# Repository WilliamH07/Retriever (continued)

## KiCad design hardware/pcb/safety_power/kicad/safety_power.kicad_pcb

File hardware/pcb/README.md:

# Printed circuit boards

Three boards, **redesigned from a clean sheet and drawn in KiCad 10**. ERC, DRC
and schematic parity are at zero on all three; none has been fabricated yet.

| Read | For |
|---|---|
| [`etat-des-lieux.md`](etat-des-lieux.md) | Status of all three, what blocks each, what an expert must review (French) |
| [`simulations.md`](simulations.md) | ngspice results for the chopper, precharge, Hall tap, VR and eFuses (French) |
| [`conception-v2.md`](conception-v2.md) | The cross-board brief: why v1 failed, principles, decisions D1–D9 (French) |
| [`outils.md`](outils.md) | The toolchain: KiCad 10 driven from the command line, the Python generator |

The first
pass (August–September 2026, EasyEDA) is archived in
[`docs/archive/pcb-v1/`](../../docs/archive/pcb-v1/): its schematic was never
functional, and parts of its specification contradicted the v1.2 corrections.

| Board | Role | Copies | Blocked by | Design brief |
|---|---|---|---|---|
| `safety_bus_distribution` | Passive CAN + `/SAFE` trunk, protected 5 V per node, no MCU | 1 of 5 | nothing — **v2.0**, ready to order | [decisions](safety_bus_distribution/decisions.md) · [brief](safety_bus_distribution/cahier-des-charges.md) |
| `motor_interface` | Hall tap to the ESP32, command path VR / DIR / EL / STOP to two ZS-X11H | 2 of 5 | **v2.0-draft**; M7, HALL_OC, P1–P3 | [decisions](motor_interface/decisions.md) · [brief](motor_interface/cahier-des-charges.md) |
| `safety_power` | Battery input, static contactor, precharge, brake chopper, INA228, DC/DC rails, SAFETY ESP32 | 1 of 5 | **v2.0-draft**; M1, M2, M10, M12, PACK_ID, P1–P3, expert review | [decisions](safety_power/decisions.md) · [brief](safety_power/cahier-des-charges.md) |

Two single-board studies for the PCBWay sponsorship (`mainboard`, `logic_board`) are
kept in [`prototypage/`](prototypage/): neither fits the 60 € budget.

Build order, from [`11-corrections-v1.2.md`](../../docs/architecture/11-corrections-v1.2.md)
part 6:

```
1  safety_bus_distribution   no blocking measurement, unlocks the CAN bench
2  M4, M5, M7 on one motor and one ZS-X11H, current-limited lab supply
3  Hall tap prototype on perfboard, one channel
4  motor_interface
5  PACK_ID, M1, M2, M10, M12 on the pack
6  safety_power
```

## Inputs for the redesign

| Source | What it fixes |
|---|---|
| [`../icd.yaml`](../icd.yaml) | Connectors, pinouts, wire colours, GPIO allocation |
| [`09-validation-composants.md`](../../docs/architecture/09-validation-composants.md) | Every part checked against its datasheet |
| [`10-spec-motor-interface.md`](../../docs/architecture/10-spec-motor-interface.md) | The two-motor board |
| [`11-corrections-v1.2.md`](../../docs/architecture/11-corrections-v1.2.md) | Safety-critical corrections C-S1 to C-S3, parts C5 to C17 |
| [`12-contacteur-statique.md`](../../docs/architecture/12-contacteur-statique.md) | Static contactor and precharge |

Corrections that a new schematic must carry, whatever the tool:

- `/SAFE` does not brake: ZS-X11H `STOP` is active low and coasts. Braking
  comes from `EL`, pulled up to `5V_BRAKE` on the loom (C-S1).
- The brake chopper is mandatory, 22 Ω / 100 W, on at 43.0 V, off at 42.3 V since v2.1; was 42.5 / 41.8 V
  (C-S2).
- Every fuse on the 42 V side is rated 58 V DC: `BF1 58V` in MIDI 498 holders,
  MRBF at the battery (C-S3).
- CAN transceiver `TCAN1042HVDR`, not `SN65HVD230` (C5).
- Three Hall lines per motor through `SN74LVC3G17`, 2.2 kΩ pull-up and
  2.2 kΩ + 10 nF filter (C7).
- `INA228` current and energy monitor (C8). eFuses chosen per voltage class
  (C10). `GPIO12` never used (C14).

## What each board folder holds

```
README.md            role, connectors, status, render
sim/                 ngspice netlists, where a block was simulated
decisions.md         every design choice and its reason (French)
build.sh, fab.sh     regenerate the KiCad project, then the fabrication files
scripts/build.py     the board, described once in Python
kicad/               generated KiCad 10 project
fab/                 Gerber zip, JLCPCB BOM and placement, schematic PDF, renders
```

Fabrication output is committed so anyone can order the boards without opening
a design tool.

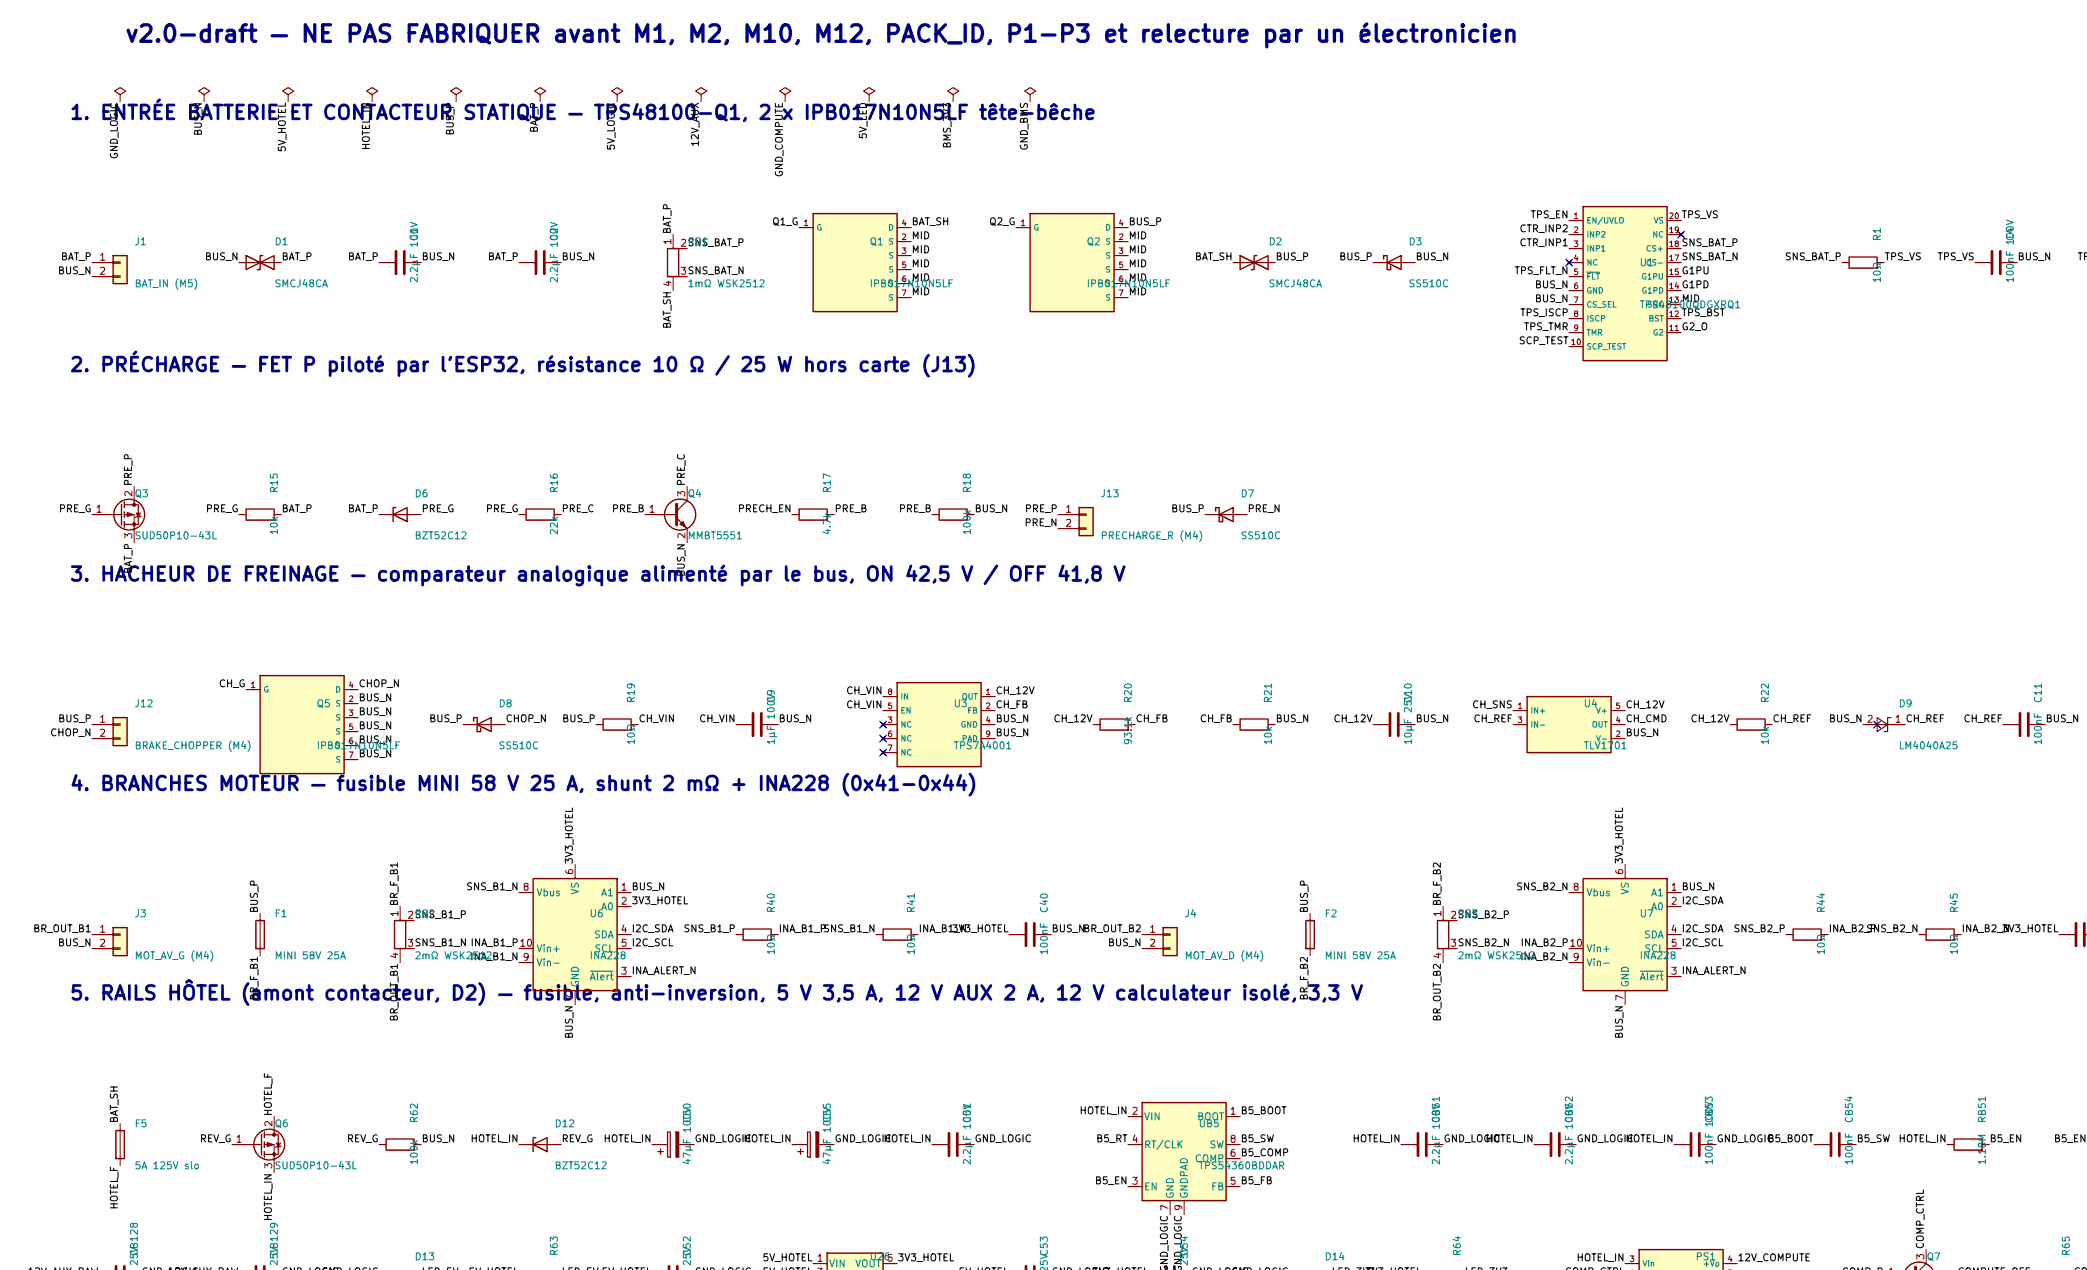
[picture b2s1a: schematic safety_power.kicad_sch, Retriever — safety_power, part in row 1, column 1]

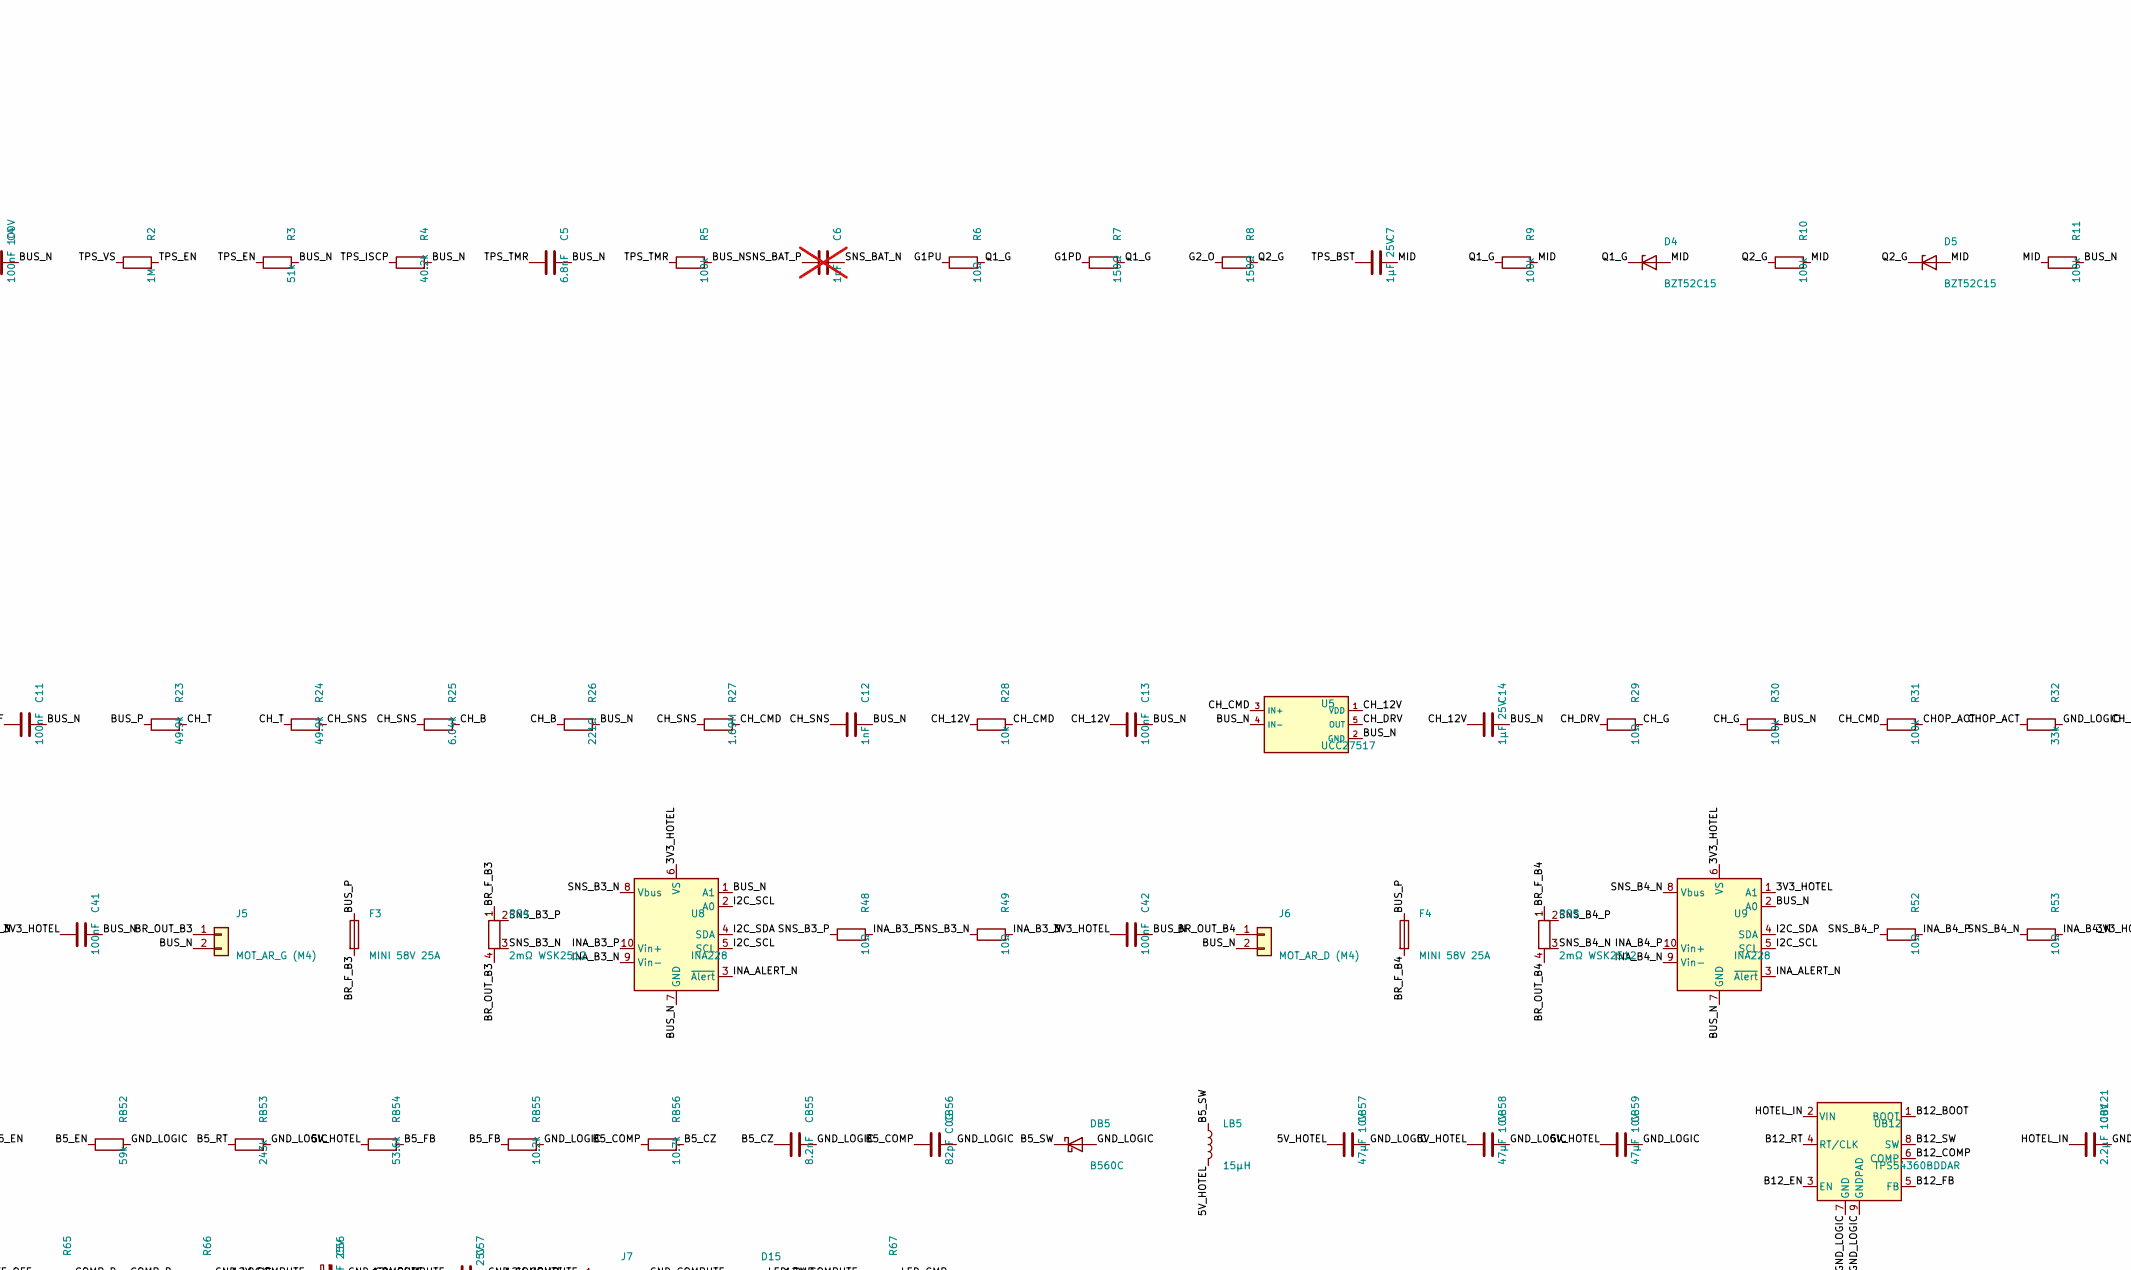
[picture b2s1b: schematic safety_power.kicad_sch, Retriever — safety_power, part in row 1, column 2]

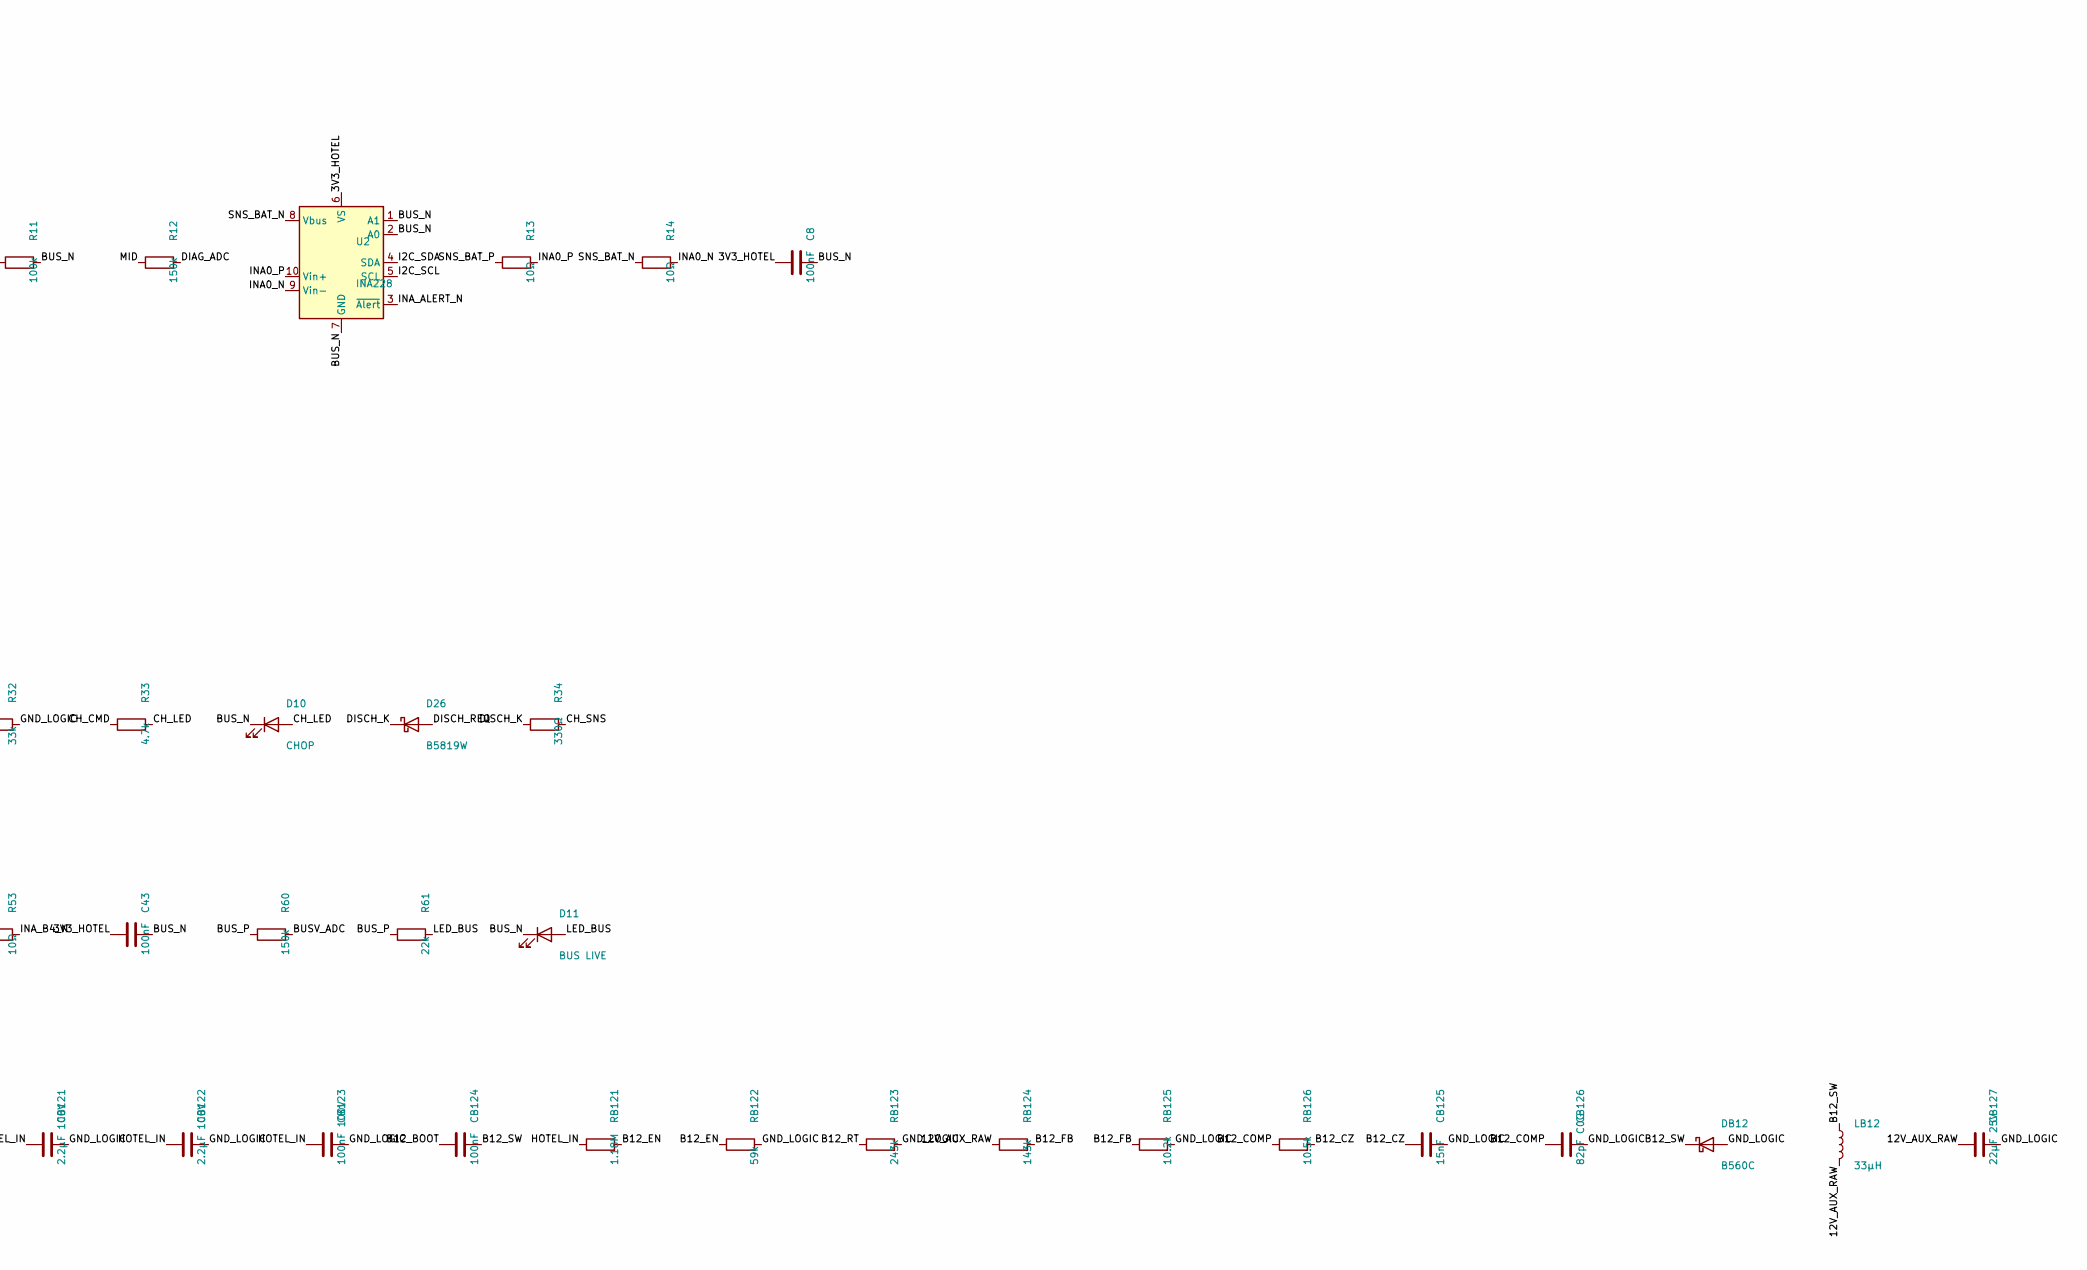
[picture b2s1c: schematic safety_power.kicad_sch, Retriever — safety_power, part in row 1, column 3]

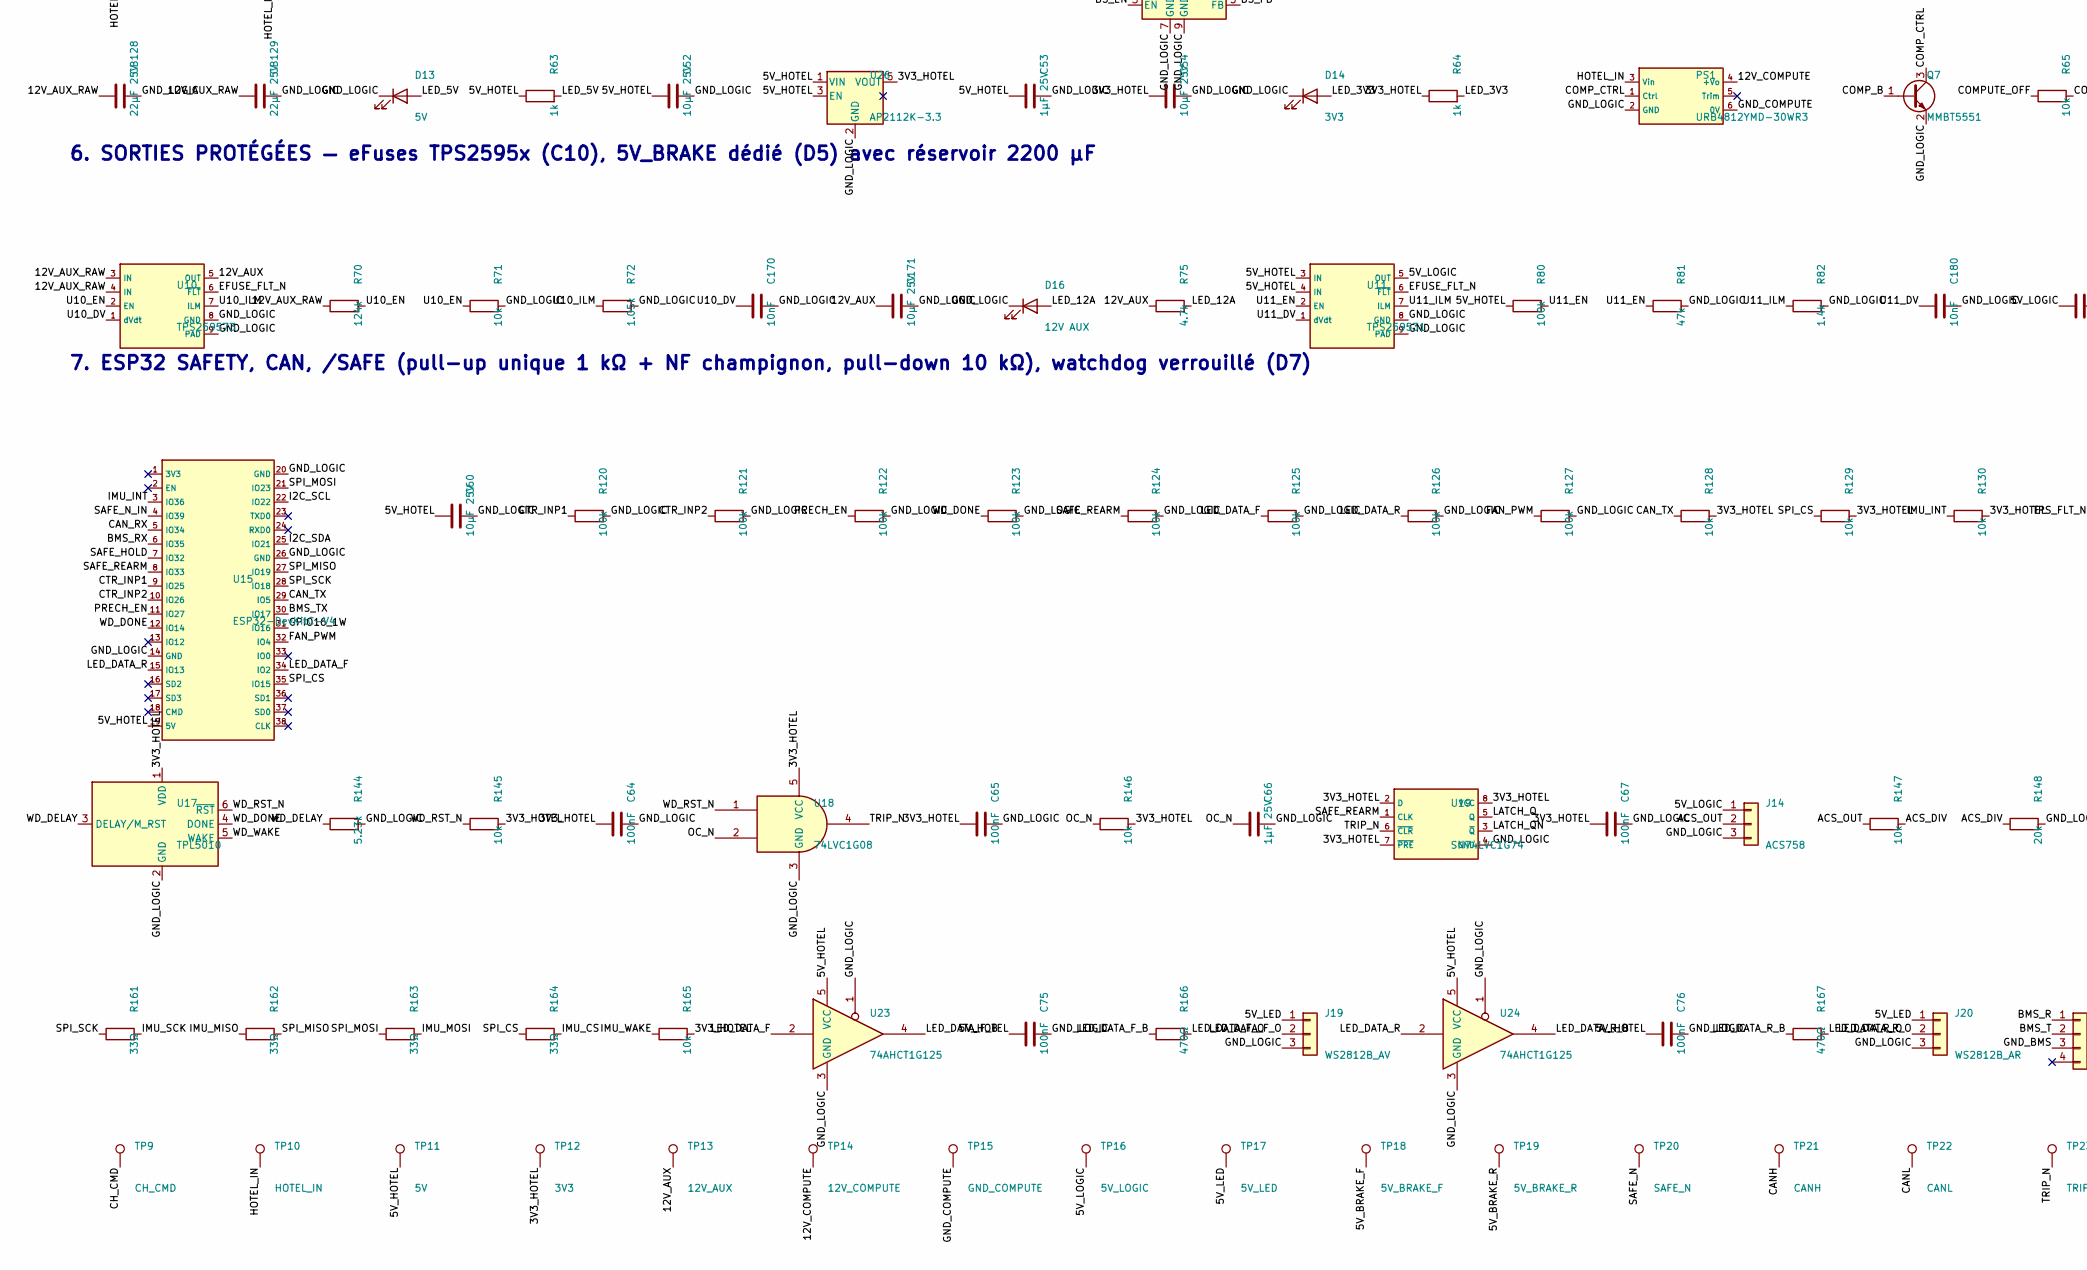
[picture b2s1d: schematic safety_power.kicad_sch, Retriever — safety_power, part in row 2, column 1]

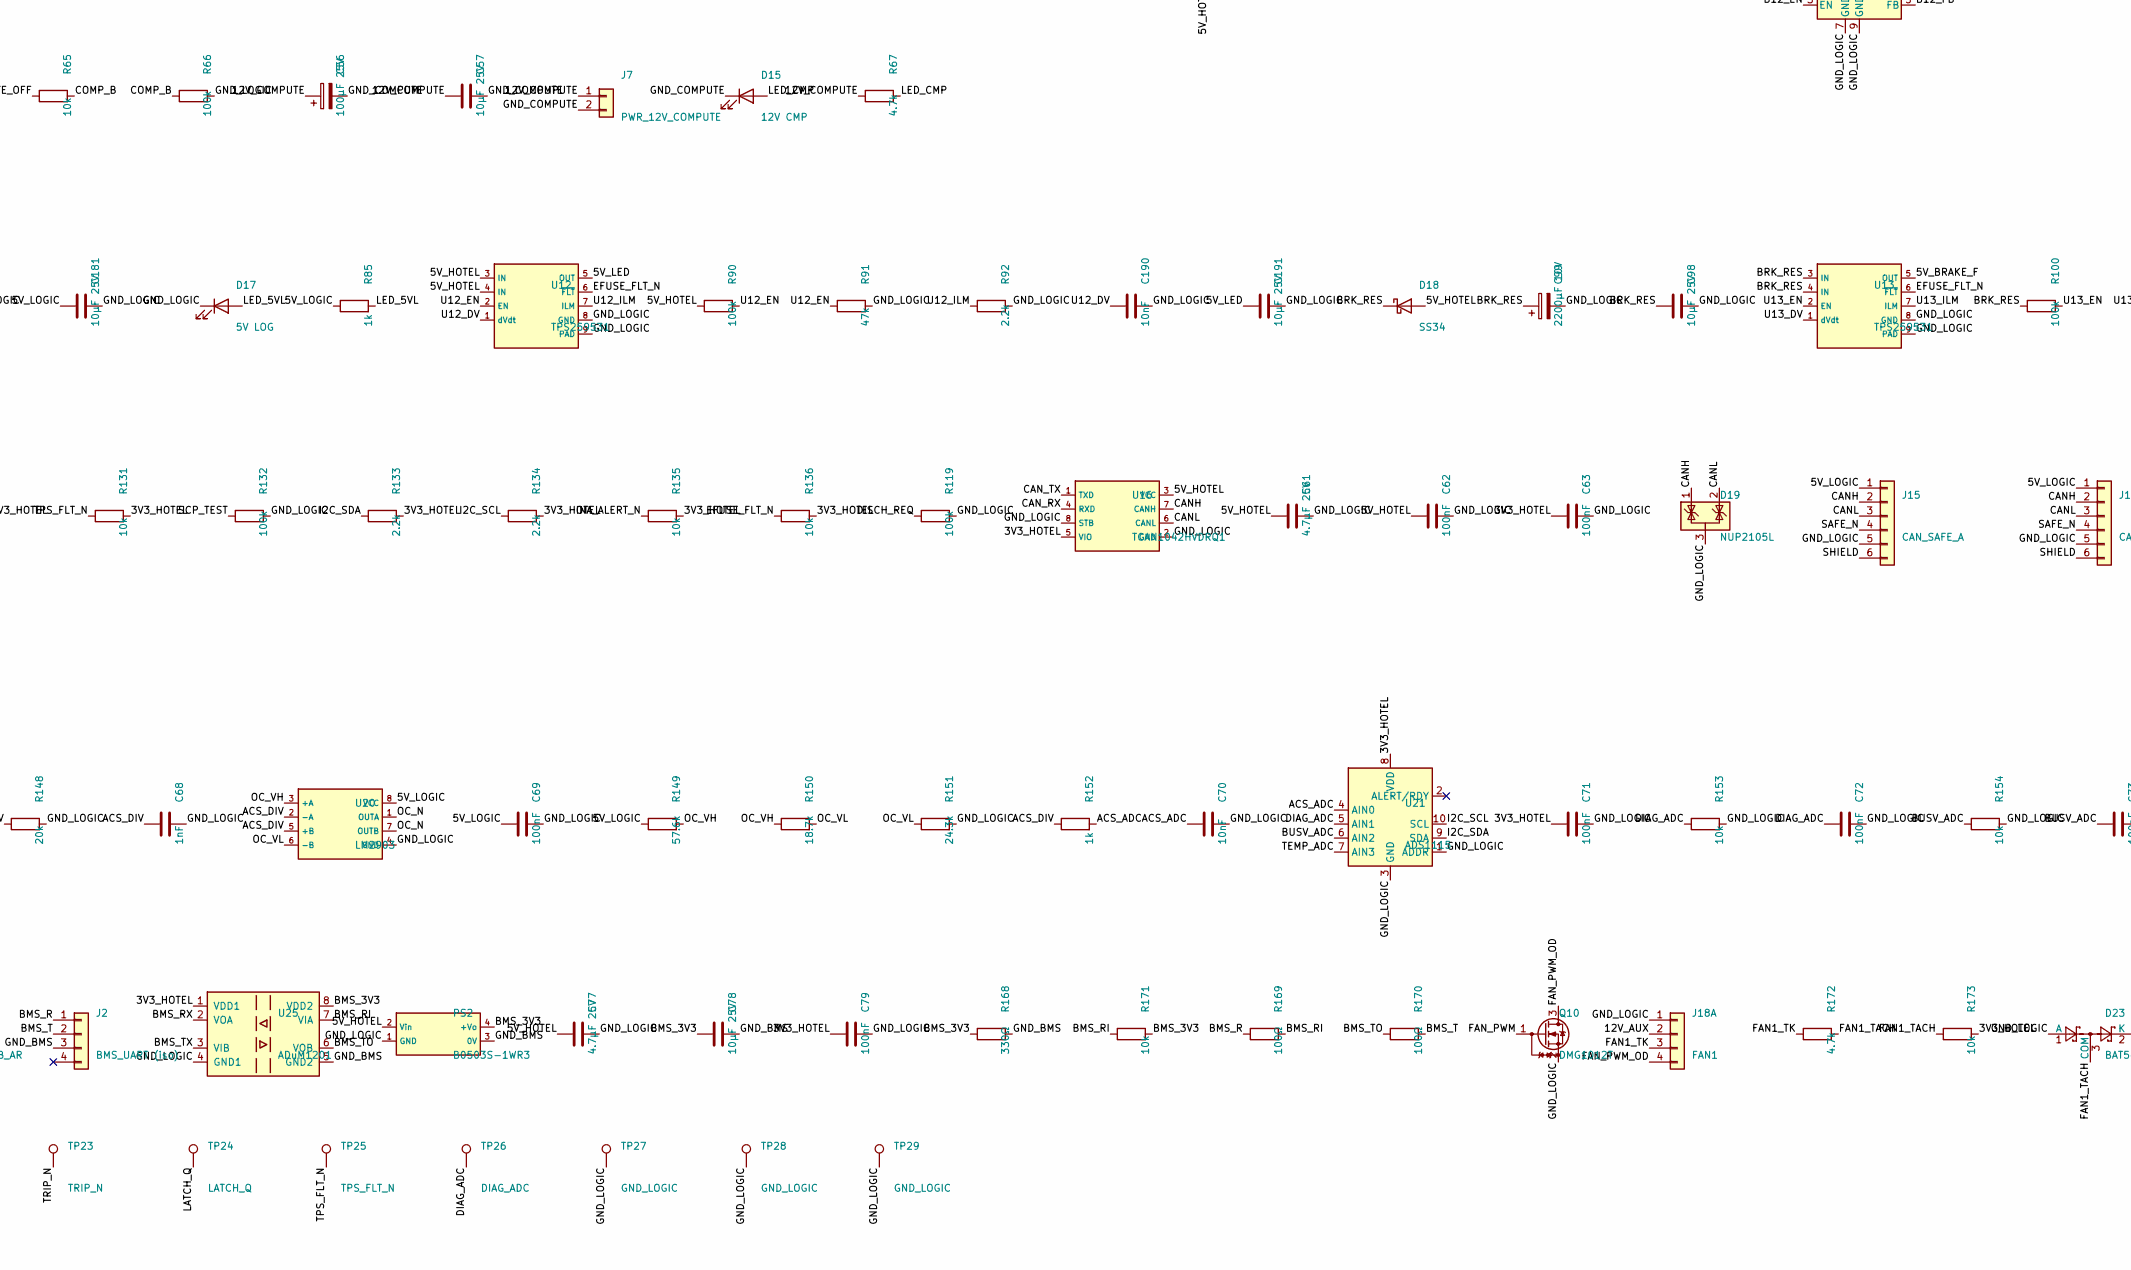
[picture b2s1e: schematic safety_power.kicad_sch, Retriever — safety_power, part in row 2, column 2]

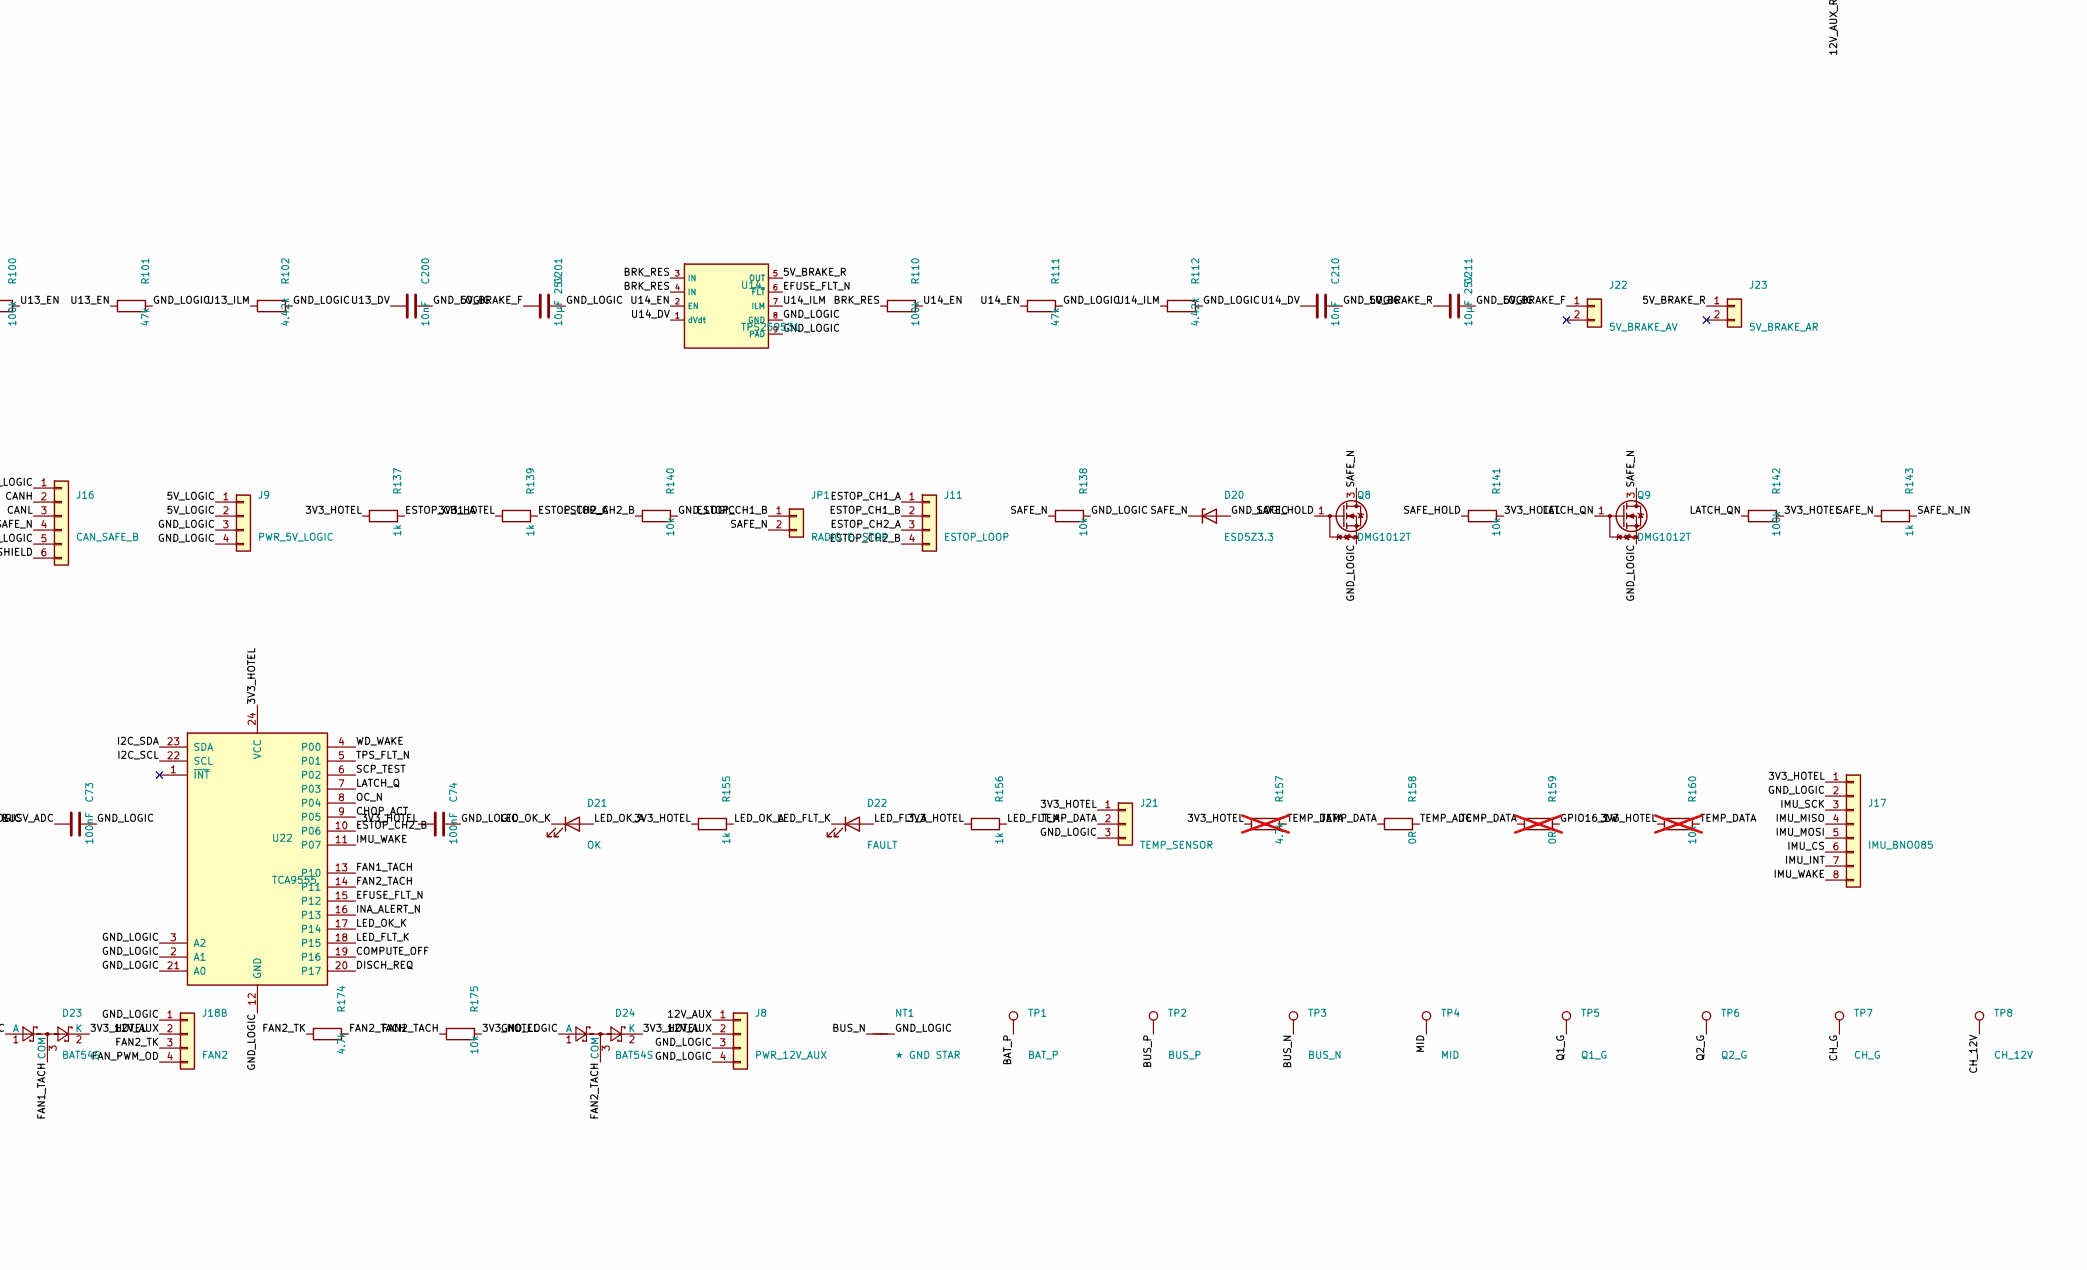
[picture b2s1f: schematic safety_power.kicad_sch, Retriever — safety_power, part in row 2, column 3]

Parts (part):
C1, C2, C51: 2.2µF 100V; C_1210_3225Metric; MPN FS32X225K101EGG; LCSC C153036
C4: 100nF 100V; C_0603_1608Metric; MPN 0603B104K101NT; LCSC C88219
C5: 6.8nF; C_0603_1608Metric; MPN 0603B682K500NT; LCSC C1631
C6: 1nF; C_0603_1608Metric; MPN CL10B102KB8NNNC; LCSC C1588; not fitted
C7, C14, C53, C66: 1µF 25V; C_0603_1608Metric; MPN CL10A105KA8NNNC; LCSC C5673
C8, C11, C13, C40, C41, C42, C43, C62, C63, C64, C65, C67, C69, C71, C72, C73, C74, C75, C76, C79: 100nF; C_0603_1608Metric; MPN CC0603KRX7R9BB104; LCSC C14663
C9: 1µF 100V; C_0805_2012Metric; MPN HMK212BC7105KGHTE; LCSC C385977
C10, C52, C54, C57, C60, C78, C98, C171, C181, C191, C201, C211: 10µF 25V; C_0805_2012Metric; MPN CL21A106KAYNNNE; LCSC C15850
C12, C68: 1nF; C_0603_1608Metric; MPN CL10B102KB8NNNC; LCSC C1588
C50, C55: 47µF 100V; CP_Elec_8x10; MPN RV100V47M8X10; LCSC C48935391
C56: 100µF 25V; CP_Elec_6.3x7.7; MPN RVT100UF25V67RV0011; LCSC C2836443
C61, C77: 4.7µF 25V; C_0805_2012Metric; MPN CL21A475KAQNNNE; LCSC C1779
C70, C170, C180, C190, C200, C210: 10nF; C_0603_1608Metric; MPN 0603B103K500NT; LCSC C57112
C99: 2200µF 10V; CP_Radial_D10.0mm_P5.00mm; MPN ERA10V2200M10X16; LCSC C49256788
CB51, CB52, CB121, CB122: 2.2µF 100V; C_1210_3225Metric; MPN FS32X225K101EGG; LCSC C153036
CB53, CB123: 100nF 100V; C_0603_1608Metric; MPN 0603B104K101NT; LCSC C88219
CB54, CB124: 100nF; C_0603_1608Metric; MPN CC0603KRX7R9BB104; LCSC C14663
CB55: 8.2nF; C_0603_1608Metric; MPN 0603B822K500NT; LCSC C1322360
CB56, CB126: 82pF C0G; C_0603_1608Metric; MPN CC0603JRNPO9BN820; LCSC C107056
CB57, CB58, CB59: 47µF 10V; C_1210_3225Metric; MPN GRM32ER71A476KE15L; LCSC C84494
CB125: 15nF; C_0603_1608Metric; MPN CC0603KRX7R9BB153; LCSC C107076
CB127, CB128, CB129: 22µF 25V; C_1210_3225Metric; MPN CL32A226KAJNNNE; LCSC C52306
D1, D2: SMCJ48CA; D_SMC; MPN SMCJ48CA bidirectional; LCSC C151287
D3, D7, D8: SS510C; D_SMC; MPN SS510C 100 V 5 A; LCSC C19229
D4, D5: BZT52C15; D_SOD-123; MPN BZT52C15; LCSC C173427
D6, D12: BZT52C12; D_SOD-123; MPN BZT52C12; LCSC C43491
D9: LM4040A25; SOT-23; MPN TI LM4040A25IDBZR; LCSC C9421
D10: CHOP; LED_0603_1608Metric; MPN KT-0603R; LCSC C2286
D11: BUS LIVE; LED_0603_1608Metric; MPN KT-0603R; LCSC C2286
D13: 5V; LED_0603_1608Metric; MPN Everlight 19-217/GHC; LCSC C72043
D14: 3V3; LED_0603_1608Metric; MPN Everlight 19-217/GHC; LCSC C72043
D15: 12V CMP; LED_0603_1608Metric; MPN Everlight 19-217/GHC; LCSC C72043
D16: 12V AUX; LED_0603_1608Metric; MPN Everlight 19-217/GHC; LCSC C72043
D17: 5V LOG; LED_0603_1608Metric; MPN Everlight 19-217/GHC; LCSC C72043
D18: SS34; D_SMA; MPN SS34; LCSC C8678
D19: NUP2105L; SOT-23; MPN onsemi NUP2105LT1G; LCSC C14486
D20: ESD5Z3.3; D_SOD-523; MPN ESD5Z3.3; LCSC C397781
D21: OK; LED_0603_1608Metric; MPN Everlight 19-217/GHC; LCSC C72043
D22: FAULT; LED_0603_1608Metric; MPN KT-0603R; LCSC C2286
D23, D24: BAT54S; SOT-23; MPN onsemi BAT54SLT1G; LCSC C19726
D26: B5819W; D_SOD-123; MPN B5819W; LCSC C8598
DB5, DB12: B560C; D_SMC; MPN Diodes B560C-13-F; LCSC C85100
F1, F2, F3, F4: MINI 58V 25A; Fuseholder_Blade_Mini_Keystone_3568; MPN Keystone 3568-20 holder + Littelfuse 09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
F5: 5A 125V slo; Fuse_Littelfuse-NANO2-451_453; MPN Littelfuse 0452005.MRL; LCSC C66503
J1: BAT_IN (M5); RingLug_M5_2P_P26; MPN plated holes, ring lugs M5
J2: BMS_UART (iso); JST_GH_SM04B-GHS-TB_1x04-1MP_P1.25mm_Horizontal; MPN JST SM04B-GHS-TB; LCSC C189895
J3: MOT_AV_G (M4); RingLug_M4_2P_P13; MPN plated holes, ring lugs M4
J4: MOT_AV_D (M4); RingLug_M4_2P_P13; MPN plated holes, ring lugs M4
J5: MOT_AR_G (M4); RingLug_M4_2P_P13; MPN plated holes, ring lugs M4
J6: MOT_AR_D (M4); RingLug_M4_2P_P13; MPN plated holes, ring lugs M4
J7: PWR_12V_COMPUTE; JST_XH_B2B-XH-A_1x02_P2.50mm_Vertical; MPN JST B2B-XH-A; LCSC C265283
J8: PWR_12V_AUX; Molex_Micro-Fit_3.0_43650-0415_1x04_P3.00mm_Vertical; MPN Molex 43650-0415; LCSC C293547
J9: PWR_5V_LOGIC; Molex_Micro-Fit_3.0_43650-0415_1x04_P3.00mm_Vertical; MPN Molex 43650-0415; LCSC C293547
J11: ESTOP_LOOP; Molex_Micro-Fit_3.0_43650-0415_1x04_P3.00mm_Vertical; MPN Molex 43650-0415; LCSC C293547
J12: BRAKE_CHOPPER (M4); RingLug_M4_2P_P13; MPN plated holes, ring lugs M4
J13: PRECHARGE_R (M4); RingLug_M4_2P_P13; MPN plated holes, ring lugs M4
J14: ACS758; Molex_Micro-Fit_3.0_43650-0315_1x03_P3.00mm_Vertical; MPN Molex 43650-0315; LCSC C293546
J15: CAN_SAFE_A; Molex_Micro-Fit_3.0_43650-0615_1x06_P3.00mm_Vertical; MPN Molex 43650-0615; LCSC C505231
J16: CAN_SAFE_B; Molex_Micro-Fit_3.0_43650-0615_1x06_P3.00mm_Vertical; MPN Molex 43650-0615; LCSC C505231
J17: IMU_BNO085; JST_GH_SM08B-GHS-TB_1x08-1MP_P1.25mm_Horizontal; MPN JST SM08B-GHS-TB; LCSC C265111
J18A: FAN1; FanPinHeader_1x04_P2.54mm_Vertical; MPN Molex 47053-1000; LCSC C240840
J18B: FAN2; FanPinHeader_1x04_P2.54mm_Vertical; MPN Molex 47053-1000; LCSC C240840
J19: WS2812B_AV; Molex_Micro-Fit_3.0_43650-0315_1x03_P3.00mm_Vertical; MPN Molex 43650-0315; LCSC C293546
J20: WS2812B_AR; Molex_Micro-Fit_3.0_43650-0315_1x03_P3.00mm_Vertical; MPN Molex 43650-0315; LCSC C293546
J21: TEMP_SENSOR; Molex_Micro-Fit_3.0_43650-0315_1x03_P3.00mm_Vertical; MPN Molex 43650-0315; LCSC C293546
J22: 5V_BRAKE_AV; Molex_Micro-Fit_3.0_43650-0215_1x02_P3.00mm_Vertical; MPN Molex 43650-0215; LCSC C293740
J23: 5V_BRAKE_AR; Molex_Micro-Fit_3.0_43650-0215_1x02_P3.00mm_Vertical; MPN Molex 43650-0215; LCSC C293740
JP1: RADIO E-STOP; PinHeader_1x02_P2.54mm_Vertical; MPN 2.54 mm 1x2 header + jumper; LCSC C492401
LB5: 15µH; L_TaiTech_TMPC1265_13.5x12.5mm; MPN Bourns SRP1265A-150M; LCSC C189912
LB12: 33µH; L_TaiTech_TMPC1265_13.5x12.5mm; MPN MDA1365-330M; LCSC C2847586
NT1: ★ GND STAR; NetTie_GND_STAR_4mm
PS1: URB4812YMD-30WR3; Mornsun_URB_YMD-30WR3_1x1in; MPN Mornsun URB4812YMD-30WR3; LCSC C22458769
PS2: B0503S-1WR3; PinHeader_1x04_P2.54mm_Vertical; MPN Mornsun B0503S-1WR3; LCSC C5369462
Q1, Q2, Q5: IPB017N10N5LF; TO-263-7_TabPin4_NoPin4; MPN Infineon IPB017N10N5LFATMA1; LCSC C3289286
Q3, Q6: SUD50P10-43L; TO-252-2; MPN SUD50P10-43L-TP; LCSC C41408040
Q4, Q7: MMBT5551; SOT-23; MPN MMBT5551; LCSC C2145
Q8, Q9, Q10: DMG1012T; SOT-523; MPN Diodes DMG1012T-7; LCSC C20512
R1, R6, R13, R14, R19, R29, R40, R41, R44, R45, R48, R49, R52, R53: 10Ω; R_0603_1608Metric; MPN 0603WAF100JT5E; LCSC C22859
R2: 1M; R_0603_1608Metric; MPN 0603WAF1004T5E; LCSC C22935
R3: 51k; R_0603_1608Metric; MPN 0603WAF5102T5E; LCSC C23196
R4: 40.2k; R_0603_1608Metric; MPN 0603WAF4022T5E; LCSC C12447
R5, R9, R10, R11, R18, R30, R31, R62, R66, R80, R90, R100, R110, R119, R120, R121, R122, R123, R124, R125, R126, R127, R132, R142: 100k; R_0603_1608Metric; MPN 0603WAF1003T5E; LCSC C25803
R7, R8: 150Ω; R_0603_1608Metric; MPN 0603WAF1500T5E; LCSC C22808
R12, R60: 150k; R_0603_1608Metric; MPN 0603WAF1503T5E; LCSC C22807
R15, R21, R22, R28, R65, R71, R128, R129, R130, R131, R135, R136, R138, R140, R141, R145, R146, R147, R153, R154, R165, R171, R173, R175: 10k; R_0603_1608Metric; MPN 0603WAF1002T5E; LCSC C25804
R16: 22k; R_0603_1608Metric; MPN 0603WAF2202T5E; LCSC C31850
R17, R33, R67, R75, R172, R174: 4.7k; R_0603_1608Metric; MPN 0603WAF4701T5E; LCSC C23162
R20: 93.1k; R_0603_1608Metric; MPN AC0603FR-0793K1L; LCSC C228101
R23, R24: 49.9k; R_0603_1608Metric; MPN 0603WAF4992T5E; LCSC C23184
R25: 6.04k; R_0603_1608Metric; MPN 0603WAF6041T5E; LCSC C25977
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
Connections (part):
/3V3_HOTEL: C8.1, C40.1, C41.1, C42.1, C43.1, C54.1, C63.1, C64.1, C65.1, C67.1, C71.1, C74.1, C79.1, D23.2 (K), D24.2 (K), J17.1, J21.1, R64.1, R128.2, R129.2, R130.2, R131.2, R133.2, R134.2, R135.2, R136.2, R137.1, R139.1, R141.2, R142.2, R145.2, R146.2, R155.1, R156.1, R157.1, R160.1, R165.2, R173.2, R175.2, TP12.1, U2.6 (VS), U6.2 (A0), U6.6 (VS), U7.6 (VS), U8.6 (VS), U9.1 (A1), U9.6 (VS), U16.5 (VIO), U17.1 (VDD), U18.5 (VCC), U19.2 (D), U19.7 (~PRE), U19.8 (VCC), U21.8 (VDD), U22.24 (VCC), U25.1 (VDD1), U26.5 (VOUT)
/5V_BRAKE_F: C201.1, J22.1, TP18.1, U13.5 (OUT)
/5V_BRAKE_R: C211.1, J23.1, TP19.1, U14.5 (OUT)
/5V_HOTEL: C52.1, C53.1, C60.1, C61.1, C62.1, C75.1, C76.1, C77.1, CB57.1, CB58.1, CB59.1, D18.2 (A), LB5.2, PS2.2 (Vin), R63.1, R80.1, R90.1, RB54.1, TP11.1, U11.3 (IN), U11.4 (IN), U12.3 (IN), U12.4 (IN), U15.19 (5V), U16.3 (VCC), U23.5 (VCC), U24.5 (VCC), U26.1 (VIN), U26.3 (EN)
/5V_LED: C191.1, J19.1, J20.1, TP17.1, U12.5 (OUT)
/5V_LOGIC: C69.1, C181.1, J9.1, J9.2, J14.1, J15.1, J16.1, R85.1, R149.1, TP16.1, U11.5 (OUT), U20.8 (VCC)
/12V_AUX: C171.1, J8.1, J8.2, J18A.2, J18B.2, R75.1, TP13.1, U10.5 (OUT)
/12V_AUX_RAW: CB127.1, CB128.1, CB129.1, LB12.2, R70.1, RB124.1, U10.3 (IN), U10.4 (IN)
/12V_COMPUTE: C56.1, C57.1, J7.1, PS1.4 (+Vo), R67.1, TP14.1
/ACS_ADC: C70.1, R152.2, U21.4 (AIN0)
/ACS_DIV: C68.1, R147.2, R148.1, R152.1, U20.2 (-A), U20.5 (+B)
/ACS_OUT: J14.2, R147.1
/B5_BOOT: CB54.1, UB5.1 (BOOT)
/B5_COMP: CB56.1, RB56.1, UB5.6 (COMP)
/B5_CZ: CB55.1, RB56.2
/B5_EN: RB51.2, RB52.1, UB5.3 (EN)
/B5_FB: RB54.2, RB55.1, UB5.5 (FB)
/B5_RT: RB53.1, UB5.4 (RT/CLK)
/B5_SW: CB54.2, DB5.1 (K), LB5.1, UB5.8 (SW)
/B12_BOOT: CB124.1, UB12.1 (BOOT)
/B12_COMP: CB126.1, RB126.1, UB12.6 (COMP)
/B12_CZ: CB125.1, RB126.2
/B12_EN: RB121.2, RB122.1, UB12.3 (EN)
/B12_FB: RB124.2, RB125.1, UB12.5 (FB)
/B12_RT: RB123.1, UB12.4 (RT/CLK)
/B12_SW: CB124.2, DB12.1 (K), LB12.1, UB12.8 (SW)
/BAT_P: C1.1, C2.1, D1.2 (A2), D6.1 (K), J1.1, Q3.3 (S), R15.2, RS1.1, TP1.1
/BAT_SH: D2.1 (A1), F5.1, Q1.4 (D), RS1.4
/BMS_3V3: C78.1, PS2.4 (+Vo), R168.1, R171.2, U25.8 (VDD2)
/BMS_R: J2.1, R169.1
/BMS_RI: R169.2, R171.1, U25.7 (VIA)
/BMS_RX: U15.6 (IO35), U25.2 (VOA)
/BMS_T: J2.2, R170.2
/BMS_TO: R170.1, U25.6 (VOB)
/BMS_TX: U15.30 (IO17), U25.3 (VIB)
/BRK_RES: C98.1, C99.1, D18.1 (K), R100.1, R110.1, U13.3 (IN), U13.4 (IN), U14.3 (IN), U14.4 (IN)
/BR_F_B1: F1.2, RS2.1
/BR_F_B2: F2.2, RS3.1
/BR_F_B3: F3.2, RS4.1
/BR_F_B4: F4.2, RS5.1
/BR_OUT_B1: J3.1, RS2.4
/BR_OUT_B2: J4.1, RS3.4
/BR_OUT_B3: J5.1, RS4.4
/BR_OUT_B4: J6.1, RS5.4
/BUSV_ADC: C73.1, R60.2, R154.1, U21.6 (AIN2)
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
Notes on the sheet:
1. ENTRÉE BATTERIE ET CONTACTEUR STATIQUE — TPS48100-Q1, 2 x IPB017N10N5LF tête-bêche
2. PRÉCHARGE — FET P piloté par l'ESP32, résistance 10 Ω / 25 W hors carte (J13)
3. HACHEUR DE FREINAGE — comparateur analogique alimenté par le bus, ON 42,5 V / OFF 41,8 V
4. BRANCHES MOTEUR — fusible MINI 58 V 25 A, shunt 2 mΩ + INA228 (0x41-0x44)
5. RAILS HÔTEL (amont contacteur, D2) — fusible, anti-inversion, 5 V 3,5 A, 12 V AUX 2 A, 12 V calculateur isolé, 3,3 V
6. SORTIES PROTÉGÉES — eFuses TPS2595x (C10), 5V_BRAKE dédié (D5) avec réservoir 2200 µF
7. ESP32 SAFETY, CAN, /SAFE (pull-up unique 1 kΩ + NF champignon, pull-down 10 kΩ), watchdog verrouillé (D7)
v2.0-draft — NE PAS FABRIQUER avant M1, M2, M10, M12, PACK_ID, P1-P3 et relecture par un électronicien

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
